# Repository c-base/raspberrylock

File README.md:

Raspberry Lock
===============

The raspberry lock is a small application that runs on a Raspberry Pi with a
PiFace shield. It reads a 4-digit user-ID and a 4-6 digit passcode from a 4x4
matrix keypad. It then sends this data to a LDAP server to check if the
entered user-id and passcode combination is correct. If the server answers with
"correct", a door is opened by switching on an electric strike with a relais.

How to kill it
--------------

```
lsof -nP -iTCP -sTCP:LISTEN | grep 8888 | cut -w -f 2 | xargs kill -9
```

Installation
--------------

Install the piface module with the Raspberry Pi configuration tool:
```
sudo raspi-config (then follow the menu to Advanced -> SPI)

sudo apt-get install python3 python3-distutils python3-setuptools python3-dev libffi-dev libssl-dev rustc build-essential git
curl -sSL https://install.python-poetry.org | python3 -
git clone <repourl>
cd <reponame>
poetry install
sudo apt install libldap-2.4-2
sudo ln -s /usr/lib/arm-linux-gnueabihf/libldap_r-2.4.so.2 /usr/lib/arm-linux-gnueabihf/libldap.so
sudo ldconfig

```

Now clone this repository and change into its subdirectory.

Copy ```config.py.sample``` to ```config.py``` and change the password/binddn/pin field/group membership test for your application.

How To Run It
----------------

```
python3 schloss.py
```

Usage
----------------

Press A, then enter your 4 digit UID code, then press A again. Now enter your 4-6 digit PIN code and hit A.
If the code was correct, the door will open.

Hardware-Setup
----------------
```
+-----------------------------------------------------------------------+
|+---------------------------------------------------------------------+|
||+-------------------------------------------------------------------+||
|||+-----------------------------------------------------------------+|||
||||  +------+.................                                      ||||
||||  |      |                :                   +---------------+  ||||
|||+---+0    |  RASPBERRY PI  :                   |    KEYPAD     |  ||||
||+----+1    +--------+       :                   |               |  ||||
|+-----+2             |       :                   | 1   2   3   F |  ||||
+------+3             |       :                   | 4   5   6   E |  ||||
      |+4             +-------+                   | 7   8   9   D |  ||||
      |+5                     |                   | A   0   B   C |  ||||
      |+6                     ^                   |               |  ||||
      |+7                     |                   |               |  ||||
      |+0V                    +                   +---++++-++++---+  ||||
      |                       |    to LEDs            |||| ||||      ||||
      |                       |      ^ ^              |||| |||+------+|||
      |        PIFACE         |   Red| |Green         |||| ||+--------+||
      |                       |      | |              |||| |+----------+|
      |                       |      | |              |||| +------------+
      | ++                  7+-------+ |              ||||
      | ||                  6+---------+              ||||
      | ||                  5+------------------------+|||
      | ||                  4+-------------------------+||
      | ||  +----+ +----+   3+--------------------------+|
      | ||  |    | |    |   2+---------------------------+
      | ||  | R0 | | R1 |   1 |
      | ||  |    | |    |   0 |
      | ++  +----+ +----+ GND |
      |   .. +++    +++  +++ :|
      +-------------||--------+	        +-------------+
                    |+------------------| DOOR OPENER |-----+ +7.5V DC
                    |		            +-------------+
                    +---------------------------------------+ - (GND)
```

Additional Links
--------------------

* PiFace documentation: http://www.farnell.com/datasheets/1684425.pdf
* The keypad that we used looks somethink like this: http://uk.farnell.com/eao/eco-16250-06/keypad-4x4-matrix-0-02a-24v-plastic/dp/1130806

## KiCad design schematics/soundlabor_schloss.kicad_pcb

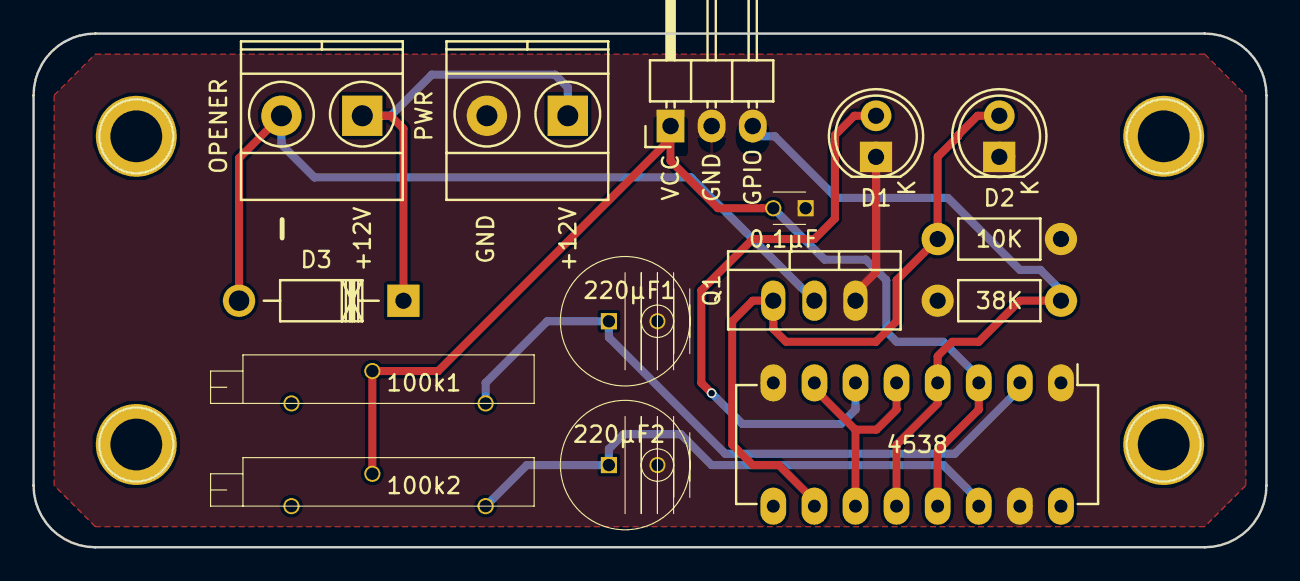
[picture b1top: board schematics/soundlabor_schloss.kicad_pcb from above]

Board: 2 copper layers, 76.2 x 31.8 mm, 15 parts (0 on the bottom side), 10 nets.

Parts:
0.1µF: C; C_Disc_D3_P2.5
10K: R; Resistor_Horizontal_RM7mm
38K: 38k; Resistor_Horizontal_RM7mm
100k1, 100k2: POT; Potentiometer_Bourns_3006P_Angular_ScrewFront
220µF1, 220µF2: CP; C_Radial_D8_L11.5_P3.5
4538: 4538; DIP-16_W7.62mm_LongPads
D1, D2: LED; LED-5MM
D3: D; Diode_DO-41_SOD81_Horizontal_RM10
P1: CONN_01X03; Pin_Header_Angled_1x03
P2, P3: CONN_01X02; TerminalBlock_Pheonix_MKDS1.5-2pol
Q1: Q_NMOS_GDS; TO-220_Neutral123_Vertical

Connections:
/+12V: D3.1, P2.1, P3.1
GND: 0.1µF.1, 10K.1, 38K.1, 220µF1.2, 220µF2.2, 4538.1, 4538.8, 4538.15, D1.1, D2.1, P1.2, P3.2, Q1.3
unnamed: 10K.2, 4538.4, 4538.12, P1.3
unnamed: 100k1.1, 220µF1.1, 4538.2
unnamed: 100k2.1, 220µF2.1, 4538.14
unnamed: 4538.6, D1.2
unnamed: 38K.2, 4538.10, D2.2, Q1.1
unnamed: D3.2, P2.2, Q1.2
unnamed: 4538.5, 4538.7, 4538.11
VCC: 0.1µF.2, 100k1.2, 100k2.2, 4538.3, 4538.13, 4538.16, P1.1

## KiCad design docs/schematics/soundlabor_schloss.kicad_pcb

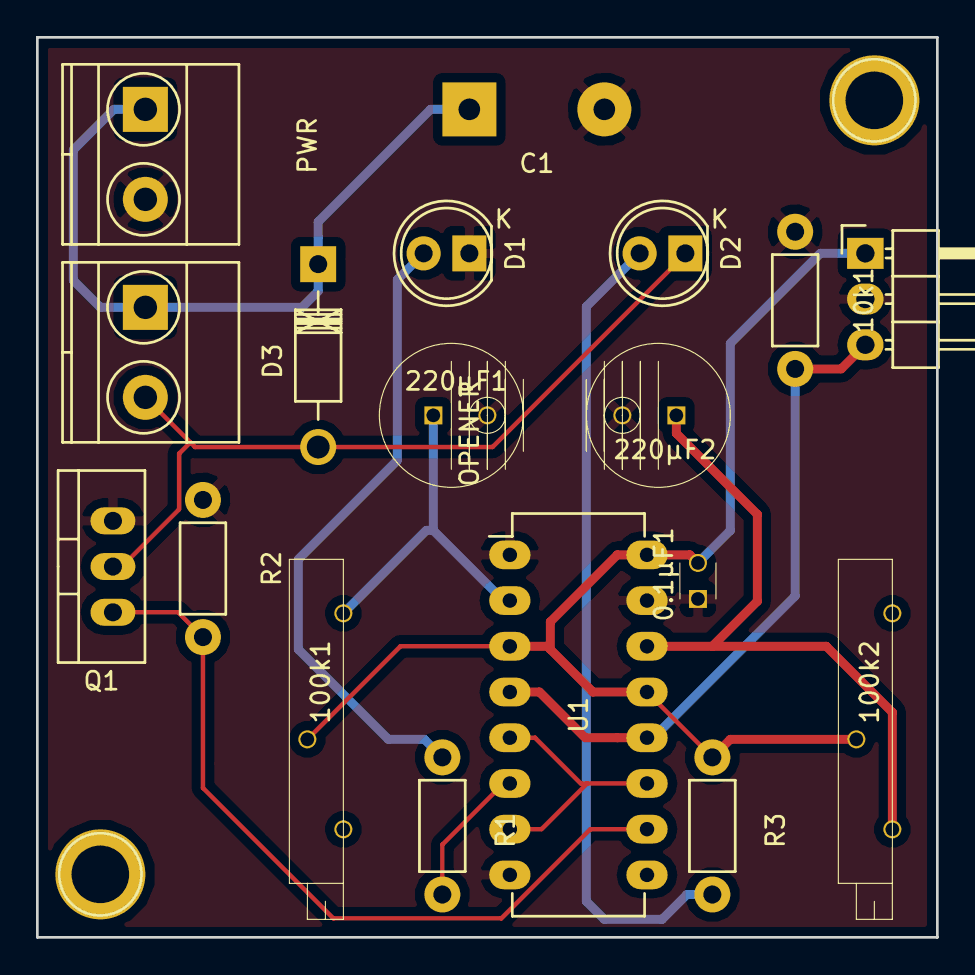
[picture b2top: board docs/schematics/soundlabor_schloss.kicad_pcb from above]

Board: 2 copper layers, 50.0 x 50.0 mm, 18 parts (0 on the bottom side), 12 nets.

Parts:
0.1µF1: C; C_Disc_D3_P2.5
10k1: R; Resistor_Horizontal_RM7mm
100k1, 100k2: POT; Potentiometer_Bourns_3006P_Angular_ScrewFront
220µF1, 220µF2: CP; C_Radial_D8_L11.5_P3.5
C1: 3300µ; ECA1EM332
D1, D2: LED; LED-5MM
D3: D; Diode_DO-41_SOD81_Horizontal_RM10
P1: CONN_01X03; Pin_Header_Angled_1x03
P2, P3: CONN_01X02; TerminalBlock_Pheonix_MKDS1.5-2pol
Q1: Q_NMOS_GDS; TO-220_Neutral123_Vertical
R1, R3: 120R; Resistor_Horizontal_RM7mm
R2: 100k; Resistor_Horizontal_RM7mm
U1: 4538; DIP-16_W7.62mm_LongPads

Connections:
+12V: C1.1, D3.1, P2.1, P3.1
GND: 0.1µF1.1, 10k1.1, 220µF1.2, 220µF2.2, C1.2, D1.1, P1.2, P2.2, Q1.3, R2.1, U1.1, U1.8, U1.15
unnamed: 100k1.1, 220µF1.1, U1.2
unnamed: 100k2.3, 220µF2.1, U1.14
unnamed: D1.2, R1.1
unnamed: D2.1, D3.2, P3.2, Q1.2
unnamed: D2.2, R3.2
unnamed: Q1.1, R2.2, U1.10
unnamed: R1.2, U1.6
unnamed: U1.5, U1.7, U1.11
PI: 10k1.2, P1.3, U1.4, U1.12
VCC: 0.1µF1.2, 100k1.2, 100k2.2, P1.1, R3.1, U1.3, U1.13, U1.16

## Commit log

2013-10-20 Initial commit, works on the raspberry pi
2013-10-20 Add Schematic
2013-10-20 R0 and R1 are the other way around
2013-10-20 Power supply and summer added
2013-10-20 Refactor state machine for simplicity and easier operation
2013-10-20 Added Link to Piface docs
2013-10-20 Fixed schematic
2013-10-20 Added Link to keypad
2013-10-25 added timeout and fixed merge request
2013-10-28 logging added
2015-05-14 dont know
2015-05-14 gpio stuff 1
2015-05-14 auslesen der tasten geht
2015-05-15 works kind of
2015-05-17 make the process nicer, repair state machine
2015-05-17 change paths, add rclocal autorestart-script
2015-09-12 Adding KiCad schematic files and such.
2015-09-12 Finishing basic PCB design. Feel free to improve on it. Uses a ground back plane and otherwise routes everything on front layer
2016-04-02 pcb done
2016-04-09 did... something
2016-04-09 improved circuit
2016-04-10 final version
2016-04-30 changed from pygame to mpv
2016-05-01 now with themes
2016-05-05 now with theme support
2016-05-05 flake8 --statistics --count --max-line-length=120 schloss.py
2016-06-11 change all the things!!
2016-06-11 forgot something
2016-06-11 now done by installer
2016-06-12 packaging stuff
2017-05-01 some changes to schematics
2018-07-15 close LDAP connections after use.
2022-10-10 add SSL to default config
2022-10-10 checkin latest dev version from hw-locc
2022-10-10 someone added docopt, I don't know why
2022-10-10 add test script
2022-10-10 done
2022-10-11 add pyproject.toml, move to poetry
2022-10-11 convert to asyncio and uvloop
2022-10-11 cool beans
2022-10-12 oh that's why
2022-10-13 make it work on rpi
2022-10-13 gogog
2022-10-13 change timeout for debounce
2022-10-13 decrease debounce interval to make lock more responsive
